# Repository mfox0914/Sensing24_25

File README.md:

# Olin Baja - 2022-2023 Electrical Projects

A variety of KiCAD schematics, PCBs, and other fun stuff from your favorite offroad vehicle team at Olin Collge of Engineering

## Current Projects
* SPI to CAN Board
	* Adapter board to convert from SPI sensor signals to CAN signals using a Raspberry Pi Pico
* Tachometer Board
	* Attempting to ressurect a techometer circut from a Baja project long ago.

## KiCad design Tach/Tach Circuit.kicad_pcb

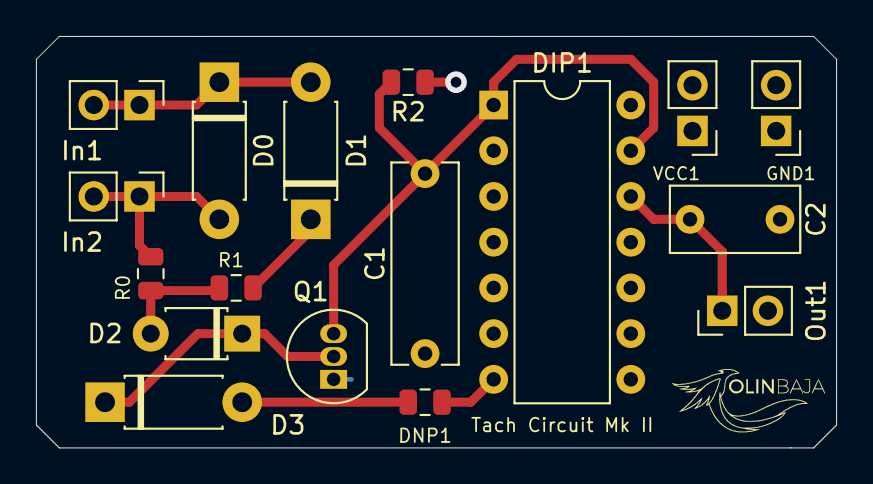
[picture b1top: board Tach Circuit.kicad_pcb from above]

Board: 2 copper layers, 44.4 x 22.9 mm, 17 parts (0 on the bottom side), 10 nets.

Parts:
C1: 2200pF; C_Rect_L11.0mm_W3.5mm_P10.00mm_MKT
C2: 39nF; C_Rect_L7.0mm_W3.5mm_P5.00mm
D0, D1: 1N4007; D_DO-41_SOD81_P7.62mm_Horizontal
D2: 1N4148; D_T-1_P5.08mm_Horizontal
D3: 1N4738; D_DO-41_SOD81_P7.62mm_Horizontal
DIP1: SN74HC14N; DIP-14_W7.62mm
DNP1: DNP; R_0805_2012Metric
GND1: GND; PinHeader_1x02_P2.54mm_Vertical
In1: Vin +; PinHeader_1x02_P2.54mm_Vertical
In2: Vin-; PinHeader_1x02_P2.54mm_Vertical
Out1: Vout; PinHeader_1x02_P2.54mm_Vertical
Q1: 2N3904; TO-92_Inline
R0, R1: 10k; R_0805_2012Metric
R2: 4.7k; R_0805_2012Metric
VCC1: 5V; PinHeader_1x02_P2.54mm_Vertical

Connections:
+5V: DIP1.14, R2.1, VCC1.1
GND: C1.2, C2.2, DIP1.7, DNP1.2, GND1.1, Q1.1
unnamed: C1.1, DIP1.1, DIP1.13, Q1.3, R2.2
unnamed: C2.1, DIP1.12, Out1.1
unnamed: D0.1, D1.2, In1.1
unnamed: D0.2, In2.1, R0.1
unnamed: D1.1, R1.2
unnamed: D2.1, D3.1, Q1.2
unnamed: D2.2, R0.2, R1.1
unnamed: D3.2, DNP1.1

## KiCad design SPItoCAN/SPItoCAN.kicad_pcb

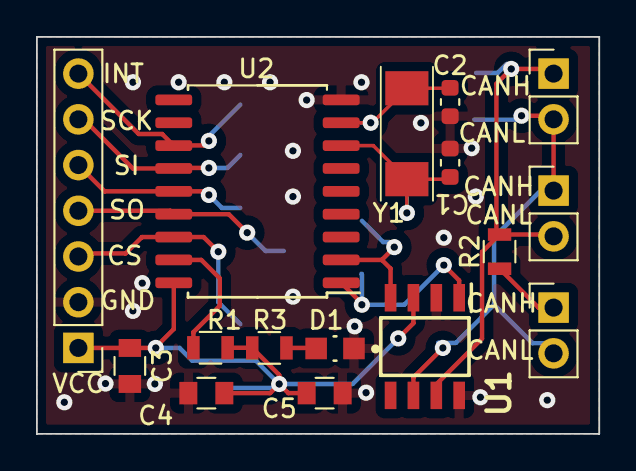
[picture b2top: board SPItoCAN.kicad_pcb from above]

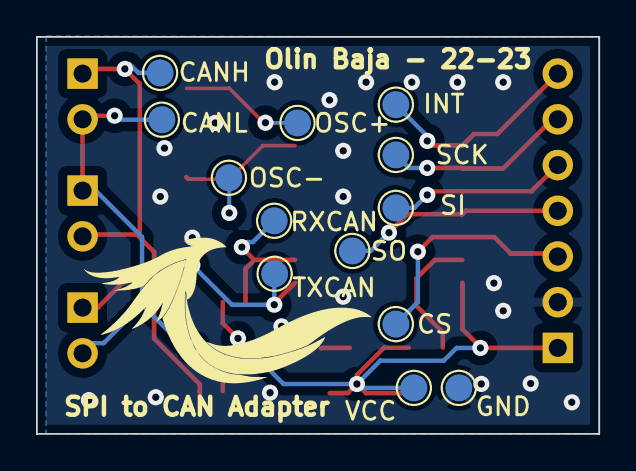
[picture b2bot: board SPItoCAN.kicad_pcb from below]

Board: 2 copper layers, 31.2 x 22.1 mm, 29 parts (13 on the bottom side), 16 nets.

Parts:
C1, C2: C_22pF; C_0603_1608Metric
C3: C_10uF_16V; C_0805_OEM
C4, C5: C_0.1uF; C_0805_OEM
CANH: Test_Point_SMD; TestPoint_Pad_D1.5mm
CANL: Test_Point_SMD; TestPoint_Pad_D1.5mm
CS: Test_Point_SMD; TestPoint_Pad_D1.5mm
D1: LED_0805_Red
GND: Test_Point_SMD; TestPoint_Pad_D1.5mm
INT: Test_Point_SMD; TestPoint_Pad_D1.5mm
J1, J2, J3: CONN_01x02; PinHeader_1x02_P2.54mm_Vertical
J4: Conn_01x07; PinHeader_1x07_P2.54mm_Vertical
OSC+: Test_Point_SMD; TestPoint_Pad_D1.5mm
OSC-: Test_Point_SMD; TestPoint_Pad_D1.5mm
R1: R_10K; R_0805_OEM
R2: R_120; R_0805_OEM
R3: R_1K; R_0805_OEM
RXCAN: Test_Point_SMD; TestPoint_Pad_D1.5mm
SCK: Test_Point_SMD; TestPoint_Pad_D1.5mm
SI: Test_Point_SMD; TestPoint_Pad_D1.5mm
SO: Test_Point_SMD; TestPoint_Pad_D1.5mm
TXCAN: Test_Point_SMD; TestPoint_Pad_D1.5mm
U1: TJA1051T-E; SOIC127P600X175-8N
U2: MCP2515-xSO; SOIC-18W_7.5x11.6mm_P1.27mm
VCC: Test_Point_SMD; TestPoint_Pad_D1.5mm
Y1: Crystal_8MHz; ABM3-8_5.0x3.2mm_P3.7mm

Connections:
/CANH: CANH.1, J2.1, J3.2, R2.2, U1.7 (CANH)
/CANL: CANL.1, J1.2, J2.2, J3.1, U1.6 (CANL)
/CS: CS.1, J4.3, U2.16 (~CS)
/INT: INT.1, J4.7, U2.12 (~INT)
/OSC+: C2.2, OSC+.1, U2.8 (OSC1), Y1.1
/OSC-: C1.2, OSC-.1, U2.7 (OSC2), Y1.2
/RXCAN: RXCAN.1, U1.4 (RXD), U2.2 (RXCAN)
/SCK: J4.6, SCK.1, U2.13 (SCK)
/SI: J4.5, SI.1, U2.14 (SI)
/SO: J4.4, SO.1, U2.15 (SO)
/TXCAN: TXCAN.1, U1.1 (TXD), U2.1 (TXCAN)
GND: C1.1, C2.1, C3.2, C4.2, C5.2, D1.1 (CATHODE), GND.1, J4.2, U1.2 (GND), U1.8 (S), U2.9 (VSS)
unnamed: D1.2 (ANODE), R3.2
unnamed: J1.1, R2.1
unnamed: R1.1, U2.17 (~RESET)
VCC: C3.1, C4.1, C5.1, J4.1, R1.2, R3.1, U1.3 (VCC), U2.18 (VDD), VCC.1

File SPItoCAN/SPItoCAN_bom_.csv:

Component,Description,Part,References,Value,Footprint,Quantity Per PCB,Datasheet,MFN,MPN,PurchasingLink,Digikey PN,Purchase Link
1,"Capacitor, 0.1uF, 50V, 5%, 0805",C_0.1uF,C4 C5,C_0.1uF,C_0805_OEM,2,http://datasheets.avx.com/X7RDielectric.pdf,DK,478-3352-1-ND,https://www.digikey.com/products/en?keywords=478-3352-1-ND,,
2,"Capacitor, 10uF, 16V, 10%, 0805",C_10uF_16V,C3,C_10uF_16V,C_0805_OEM,1,http://www.samsungsem.com/kr/support/product-search/mlcc/__i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,DK,1276-2399-1-ND,https://www.digikey.com/product-detail/en/samsung-electro-me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,,
3,"Capacitor, 18pF, 10V, 1%, 0603",C_18pF,C1 C2,C_22pF,C_0603_1608Metric,2,https://www.vishay.com/docs/28548/vjw1bcbascomseries.pdf,DK,720-1660-1-ND,https://www.digikey.com/product-detail/en/vishay-vitramon/VJ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,,
4,LED_0805_Red,LED_0805_Red,D1,LED_0805_Red,LED_0805_Red,1,https://docs.broadcom.com/docs/AV02-0112EN,Avago,HSMC-C170,https://www.digikey.com/product-detail/en/osram-opto-semicon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,516-1428-1-ND,
5,CONN HEADER 2 POS 2.54mm,CONN_01x02,J1 J2 J3,CONN_01x02,PinHeader_1x02_P2.54mm_Vertical,3,https://katalog.we-online.de/em/datasheet/6130xx11121.pdf,DK,732-5315-ND,,,
6,,Conn_01x07,J4,Conn_01x07,PinHeader_1x07_P2.54mm_Vertical,1,https://www.we-online.com/katalog/datasheet/6130xx11121.pdf,Würth Elektronik,61300711121,https://www.digikey.com/en/products/detail/61300711121/732-5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,,
7,,R_10K,R1,R_10K,R_0805_OEM,1,http://www.bourns.com/data/global/pdfs/CRS.pdf,DK,CRS0805-FX-1002ELFCT-ND,https://www.digikey.com/products/en?keywords=CRS0805-FX-1002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,,
8,,R_120,R2,R_120,R_0805_OEM,1,https://www.mouser.com/datasheet/2/315/AOA0000C304-1149620.pdf,DK,667-ERJ-6ENF1200V,https://www.mouser.com/ProductDetail/Panasonic-Industrial-De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,,
9,,R_1K,R3,R_1K,R_0805_OEM,1,https://www.seielect.com/Catalog/SEI-rncp.pdf,DK,RNCP0805FTD1K00CT-ND,https://www.digikey.com/products/en?keywords=RNCP0805FTD1K00CT-ND,,
10,"Stand-Alone CAN Controller with SPI Interface, SOIC-18",MCP2515-xSO,U2,MCP2515-xSO,SOIC-18W_7.5x11.6mm_P1.27mm,1,https://ww1.microchip.com/downloads/en/DeviceDoc/MCP2515-Sta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,,MCP2515T-I/SO,https://www.digikey.com/en/products/detail/microchip-technol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,MCP2515T-I/SODKR-ND,
11,,TJA1050T,U1,TJA1051T-E,SOIC127P600X175-8N,1,https://www.mouser.com/datasheet/2/302/TJA1050-1127967.pdf,,"TJA1050T/CM,118",https://www.mouser.com/ProductDetail/NXP-Semiconductors/TJA1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,,
12,CRYSTAL 8.0000MHZ 18PF SMD,Crystal_8MHz,Y1,Crystal_8MHz,ABM3-8_5.0x3.2mm_P3.7mm,1,https://abracon.com/Resonators/abm3.pdf,DK,535-10630-1-ND,https://www.digikey.com/product-detail/en/abracon-llc/ABM3-8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,,
,,,,,,,,,,,,
,,,,,,,,,,,,
,,,,,,,,,,,,
,,,,,,,,,,,,
,,,,,,,,,,,,
Component Groups:,12,,,,,,,,,,,
Component Count:,16,,,,,,,,,,,
Fitted Components:,16,,,,,,,,,,,
Number of PCBs:,1,,,,,,,,,,,
Total components:,16,,,,,,,,,,,
Schematic Version:,,,,,,,,,,,,
Schematic Date:,,,,,,,,,,,,
PCB Variant:,default,,,,,,,,,,,
BoM Date:,1/25/2023 20:43,,,,,,,,,,,
Schematic Source:,SPItoCAN.kicad_sch,,,,,,,,,,,
KiCad Version:,Eeschema (6.0.7),,,,,,,,,,,

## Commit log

2022-09-28 Created SPI to CAN schematic and board design
2022-10-05 Added SPI to CAN schematic and PCB KiCAD files
2022-10-18 Cleaned up PCB layout, added ground plane
2022-10-19 cleaned up pcb, improved silkscreen, ran test gerber export
2022-10-27 cleaned up layout; replaced LED; generated BOM
2022-11-03 Imported tach circut
2022-11-10 Fixed some wiring & routing across the board; added explanatory notes to schematic
2022-12-06 Added test for Pico W's
2022-12-13 Began tweaks to make everything fit within JLCPCB capabilites
2023-01-25 Further updated PCB to meet JLCPCB capabilites. Pushing etc. Tach files
2023-02-08 Final updates and gerber for board production
    Updated so board fits into breadboard and other misc. updates before generating gerbers
2023-02-08 Inital schematic for ride height sensor protoboard
2023-03-09 Add PicoCANCode base
2023-03-21 Update .gitignore, Add SPItoCAN Schematic
2023-03-21 Add ability to set board identity by DIP switch
2023-04-20 Update firmware to work with DIP switches
2023-04-25 Update RHS schematic
2025-03-12 Adding Ride Height Sensor BLE code - currently not working
